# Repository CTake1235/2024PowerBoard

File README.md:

# 2024PowerBoard
## 緊急停止基板 designed by しーたけ
- 安価で制作が容易（面実装部品は1点のみ）
- 24V/30Aに対応
- ヒューズで過電流を保護
## LED説明
- BATT
  - バッテリー挿入時点灯
  - 作業終了時に切れていることを確認しましょう
- +5V
  - 5V電源供給時に点灯
  - バッテリ接続中消灯の場合DCDCに異常がある可能性があります
- SIG
  - マイコンからの駆動電源オン信号（+3V3HIGH）で点灯
  - 消灯の場合マイコンからの信号がありません
- PWR
  - 駆動電源オン（FETオン）時に点灯
  - 他LEDが正常、駆動電源オン信号で消灯の場合FETに異常があるかもしれません
  - または、ヒューズが飛んでいる可能性があります

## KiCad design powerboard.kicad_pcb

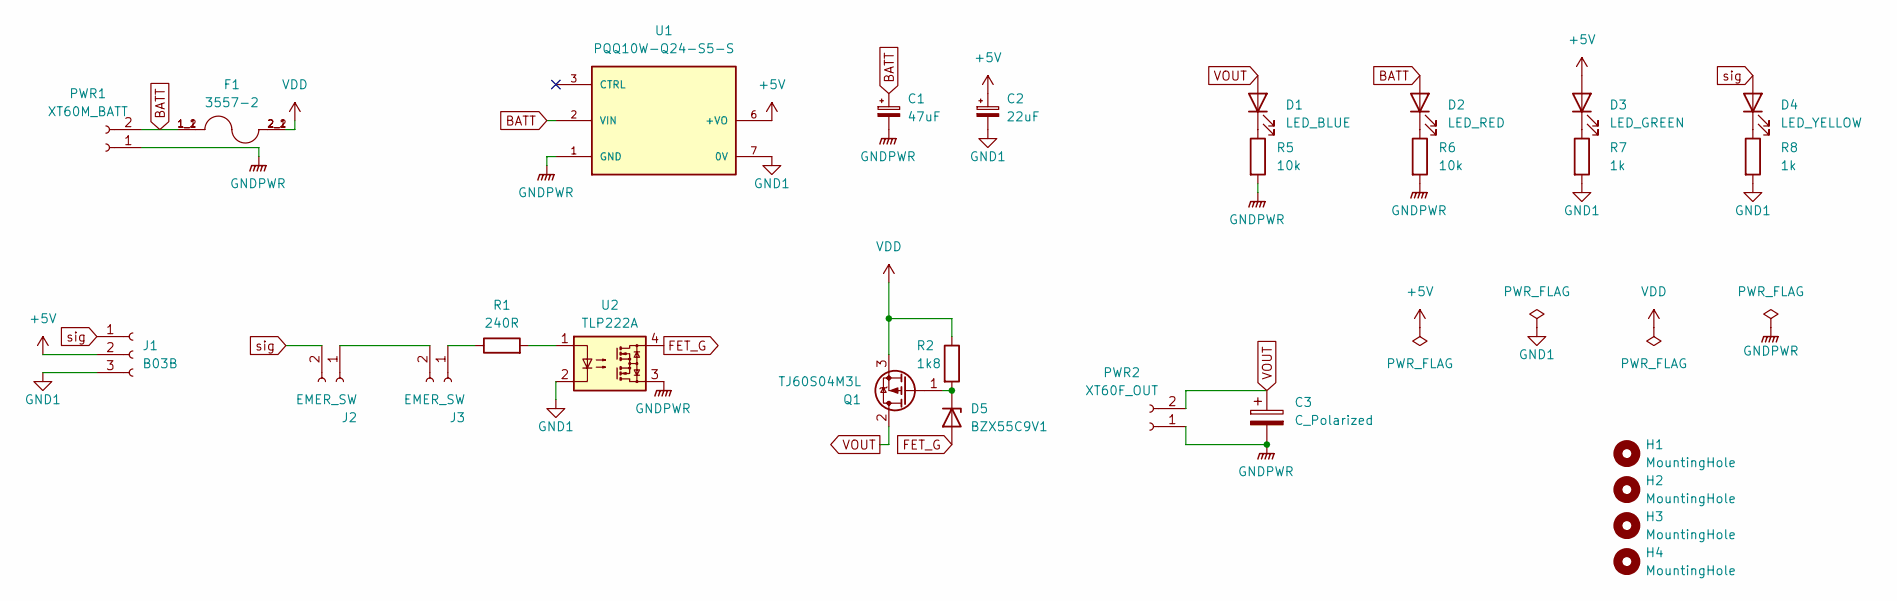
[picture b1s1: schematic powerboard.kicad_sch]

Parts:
C1: 47uF; CP_Radial_D6.3mm_P2.50mm
C2: 22uF; CP_Radial_D5.0mm_P2.00mm
C3: C_Polarized; CP_Radial_D16.0mm_P7.50mm
D1: LED_BLUE; LED_D3.0mm
D2: LED_RED; LED_D3.0mm
D3: LED_GREEN; LED_D3.0mm
D4: LED_YELLOW; LED_D3.0mm
D5: BZX55C9V1; D_DO-35_SOD27_P7.62mm_Horizontal
F1: 3557-2; FUSE_3557-2; PARTREV D
H1, H2, H3, H4: MountingHole; MountingHole_3.2mm_M3_Pad_Via
J1: B03B; JST_XA_B03B-XASK-1_1x03_P2.50mm_Vertical
J2, J3: EMER_SW; JST_XA_B02B-XASK-1_1x02_P2.50mm_Vertical
PWR1: XT60M_BATT; AMASS_XT60PW-M_1x02_P7.20mm_Horizontal
PWR2: XT60F_OUT; AMASS_XT60PW-F_1x02_P7.20mm_Horizontal
Q1: TJ60S04M3L; TO-252-2
R1: 240R; R_Axial_DIN0207_L6.3mm_D2.5mm_P7.62mm_Horizontal
R2: 1k8; R_Axial_DIN0207_L6.3mm_D2.5mm_P7.62mm_Horizontal
R5, R6: 10k; R_Axial_DIN0207_L6.3mm_D2.5mm_P7.62mm_Horizontal
R7, R8: 1k; R_Axial_DIN0207_L6.3mm_D2.5mm_P7.62mm_Horizontal
U1: PQQ10W-Q24-S5-S; CONV_PQQ10W-Q24-S5-S; PARTREV 1.0
U2: TLP222A; DIP-4_W7.62mm

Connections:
+5V: C2.1, D3.2 (A), J1.2, U1.6 (+VO)
BATT: C1.1, D2.2 (A), F1.1_1, F1.1_2, PWR1.2, U1.2 (VIN)
FET_G: D5.2 (A), U2.4
GND1: C2.2, J1.3, R7.2, R8.2, U1.7 (0V), U2.2
GNDPWR: C1.2, C3.2, PWR1.1, PWR2.1, R5.2, R6.2, U1.1 (GND), U2.3
unnamed: D1.1 (K), R5.1
unnamed: D2.1 (K), R6.1
unnamed: D3.1 (K), R7.1
unnamed: D4.1 (K), R8.1
unnamed: D5.1 (K), Q1.1 (G), R2.2
unnamed: J2.1, J3.2
unnamed: J3.1, R1.1
unnamed: R1.2, U2.1
VDD: F1.2_1, F1.2_2, Q1.3 (S), R2.1
VOUT: C3.1, D1.2 (A), PWR2.2, Q1.2 (D)
sig: D4.2 (A), J1.1, J2.2

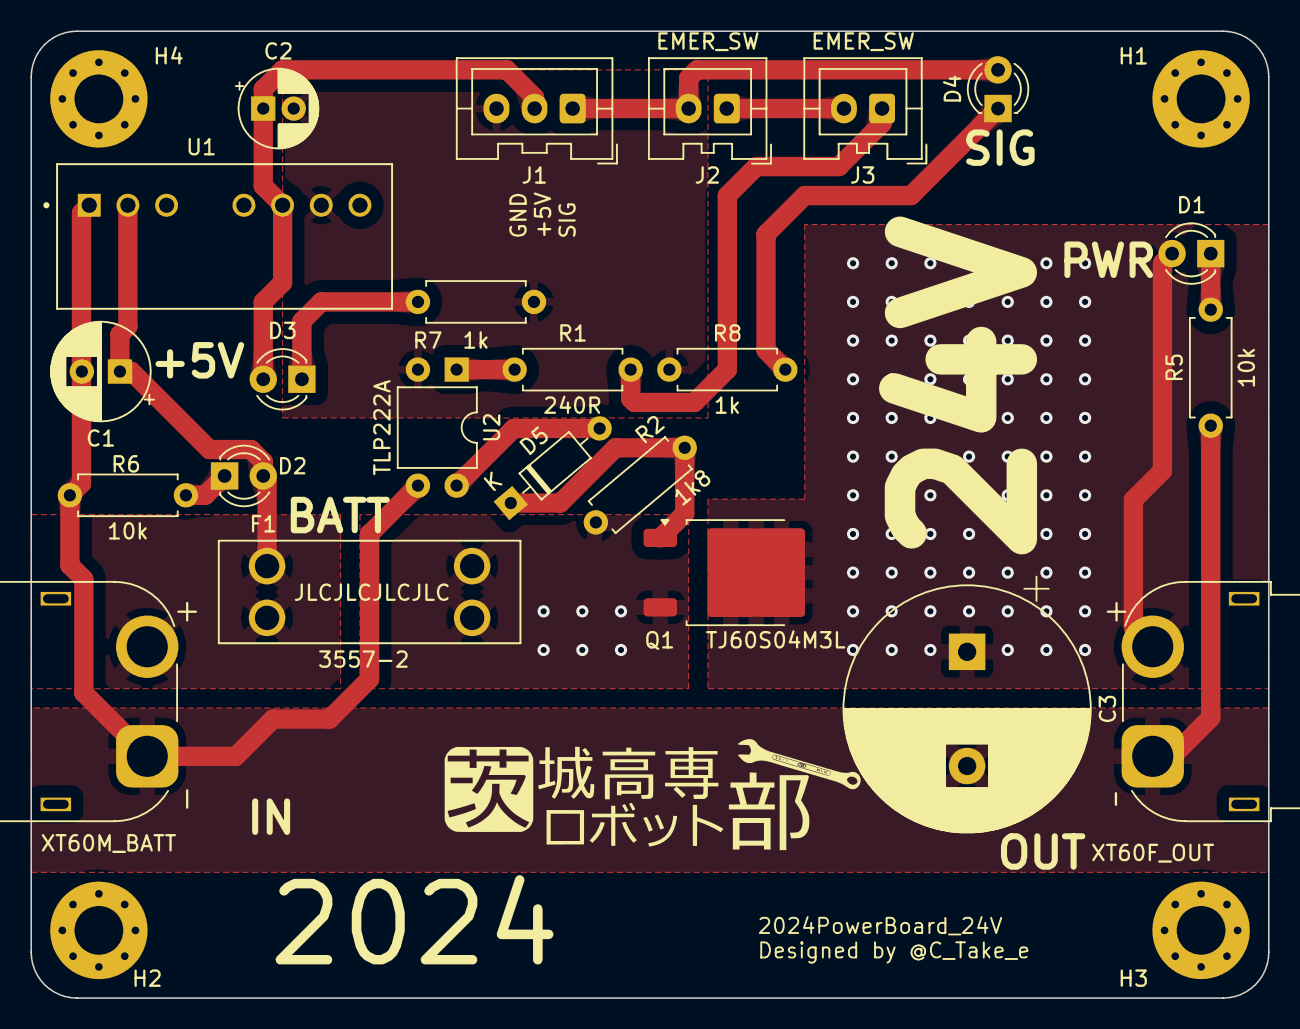
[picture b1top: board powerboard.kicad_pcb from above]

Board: 2 copper layers, 81.3 x 63.5 mm, 27 parts (0 on the bottom side), 16 nets.

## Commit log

2024-04-05 gitignore: LCK files will be ignored
2024-04-06 pcb/sch: add a hole, silks
2024-04-06 sch: change Capacitance C1 (Power)
2024-04-06 pcb: update with sch, add CUTE RESISTOR
2024-04-06 pcb: add vias
2024-04-06 pdf: update with pcb
2024-04-06 gitignore: add "*.zip"
2024-04-06 pcb/pdf: printed gerb
2024-04-07 pcb: change angle of CUTE RESISTOR
2024-04-08 pcb: add teardrops
2024-04-08 pcb: put vias under FET
2024-04-08 pdf:update
2024-04-08 pcb:add vias on VOUT, from FET to OUT
2024-04-08 pcb: moved silk of FET value
2024-04-09 pcb: make more margin between J2 & R3
2024-04-09 Revert "pcb: make a margin between J2 & R3"
    This reverts commit 403c4a9d61e7e79612fd97e349d6792e48dc765a.
2024-04-09 pcb: make a margin
2024-04-09 pcb: add vias behind source
2024-04-09 pcb: make the outline wider, move holes
2024-04-09 pcb: Leave space between J1, J2, and J3
2024-04-09 pdf: Update
2024-04-09 pcb/sch: Add FET
2024-04-09 Revert "pcb/sch: Add FET"
    This reverts commit 0032eebc1d6eb9ed2a957a3795ce5049efafd74e.
2024-04-09 pcb: Delete vias under FET
2024-04-09 pcb: Delete vias under a FET
    This reverts commit e1503daf84bd5df3be65f05229be8e469e7dccfe.
2024-04-09 pcb: BIG VOUT
2024-04-09 pcb: BIGGER VOUT
2024-04-09 pcb: Small fix for GND1 zone
2024-04-10 pcb:Finishing touches
2024-05-03 PCB: 分圧抵抗を追加、アノテーションをリセット
2024-05-03 PCB: DCDCを変更
2024-05-03 PCB: DCDCの位置調整
2024-05-03 PDF: SCH/PCBの更新を反映
2024-05-03 PCB: 微調整
2024-05-03 PDF: 更新
2024-05-18 発注用にゾーン塗りなおし
2024-05-18 クソデカ24Vシルク追加
2024-08-10 ツェナーで定電圧チャレンジ
2024-08-10 ツェナー回り修正、DCDC入力コンデンサ位置変更
2024-08-10 コンデンサ追加、フップリ修正
2024-08-13 あれこれ
